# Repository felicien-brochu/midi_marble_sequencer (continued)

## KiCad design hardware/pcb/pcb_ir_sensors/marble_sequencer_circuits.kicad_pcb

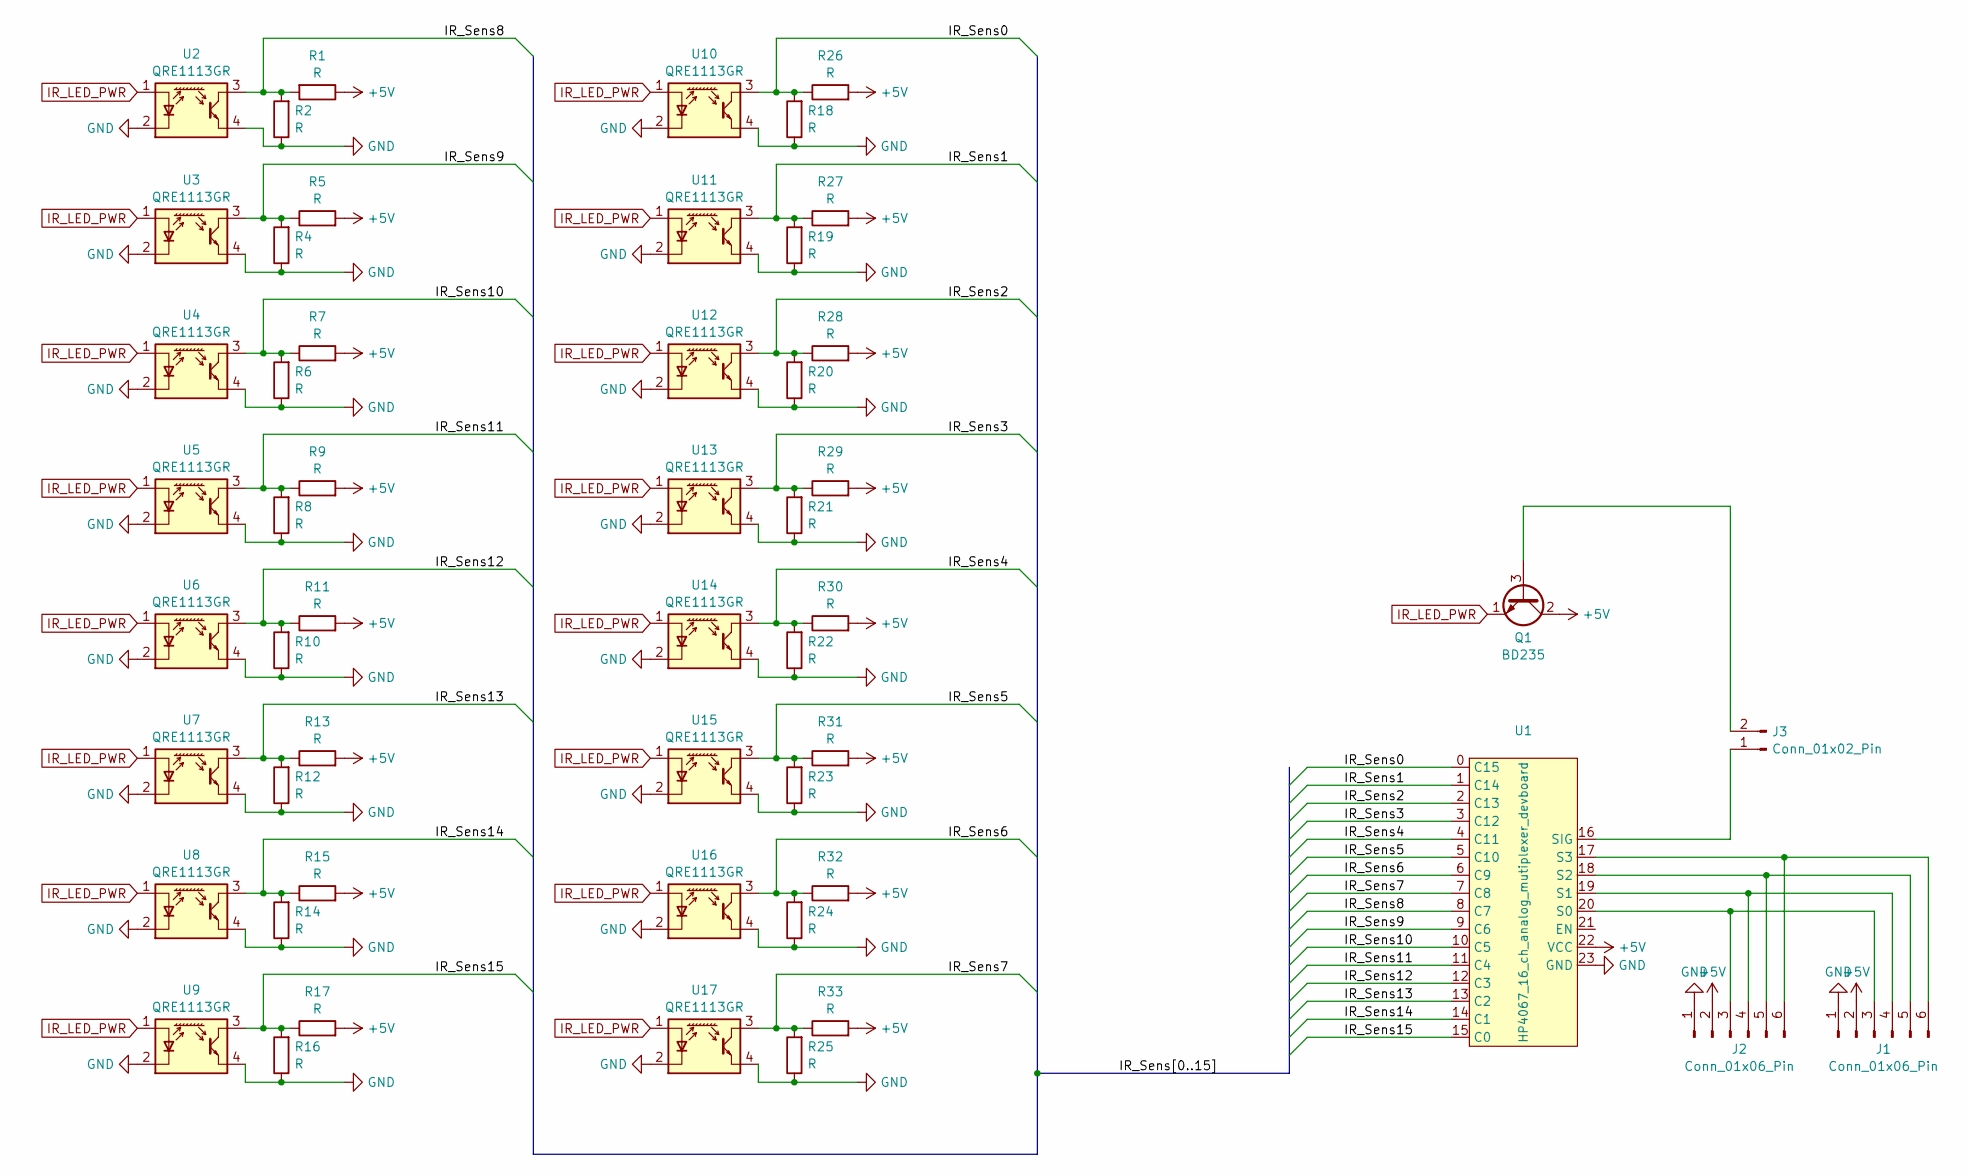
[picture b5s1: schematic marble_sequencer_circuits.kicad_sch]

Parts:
J1, J2: Conn_01x06_Pin; PinHeader_1x06_P2.54mm_Vertical
J3: Conn_01x02_Pin; PinHeader_1x02_P2.54mm_Vertical
Q1: BD235; TO-126-3_Vertical
R1, R2, R4, R5, R6, R7, R8, R9, R10, R11, R12, R13, R14, R15, R16, R17, R18, R19, R20, R21, R22, R23, R24, R25, R26, R27, R28, R29, R30, R31, R32, R33: R; R_Axial_DIN0207_L6.3mm_D2.5mm_P10.16mm_Horizontal_BIG_PADS
U1: HP4067_16_ch_analog_mutiplexer_devboard
U2, U3, U4, U5, U6, U7, U8, U9, U10, U11, U12, U13, U14, U15, U16, U17: QRE1113GR

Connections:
+5V: J1.2, J2.2, Q1.2 (C), R1.1, R5.2, R7.2, R9.2, R11.2, R13.2, R15.2, R17.2, R26.2, R27.2, R28.2, R29.2, R30.2, R31.2, R32.2, R33.2, U1.22 (VCC)
/IR_Sens0: R18.2, R26.1, U1.0 (C15), U10.3
/IR_Sens1: R19.2, R27.1, U1.1 (C14), U11.3
/IR_Sens2: R20.2, R28.1, U1.2 (C13), U12.3
/IR_Sens3: R21.2, R29.1, U1.3 (C12), U13.3
/IR_Sens4: R22.2, R30.1, U1.4 (C11), U14.3
/IR_Sens5: R23.2, R31.1, U1.5 (C10), U15.3
/IR_Sens6: R24.2, R32.1, U1.6 (C9), U16.3
/IR_Sens7: R25.2, R33.1, U1.7 (C8), U17.3
/IR_Sens8: R1.2, R2.2, U1.8 (C7), U2.3
/IR_Sens9: R4.2, R5.1, U1.9 (C6), U3.3
/IR_Sens10: R6.2, R7.1, U1.10 (C5), U4.3
/IR_Sens11: R8.2, R9.1, U1.11 (C4), U5.3
/IR_Sens12: R10.2, R11.1, U1.12 (C3), U6.3
/IR_Sens13: R12.2, R13.1, U1.13 (C2), U7.3
/IR_Sens14: R14.2, R15.1, U1.14 (C1), U8.3
/IR_Sens15: R16.2, R17.1, U1.15 (C0), U9.3
GND: J1.1, J2.1, R2.1, R4.1, R6.1, R8.1, R10.1, R12.1, R14.1, R16.1, R18.1, R19.1, R20.1, R21.1, R22.1, R23.1, R24.1, R25.1, U1.23 (GND), U2.2 (K), U2.4, U3.2 (K), U3.4, U4.2 (K), U4.4, U5.2 (K), U5.4, U6.2 (K), U6.4, U7.2 (K), U7.4, U8.2 (K), U8.4, U9.2 (K), U9.4, U10.2 (K), U10.4, U11.2 (K), U11.4, U12.2 (K), U12.4, U13.2 (K), U13.4, U14.2 (K), U14.4, U15.2 (K), U15.4, U16.2 (K), U16.4, U17.2 (K), U17.4
IR_LED_PWR: Q1.1 (E), U2.1 (A), U3.1 (A), U4.1 (A), U5.1 (A), U6.1 (A), U7.1 (A), U8.1 (A), U9.1 (A), U10.1 (A), U11.1 (A), U12.1 (A), U13.1 (A), U14.1 (A), U15.1 (A), U16.1 (A), U17.1 (A)
unnamed: J1.3, J2.3, U1.20 (S0)
unnamed: J1.4, J2.4, U1.19 (S1)
unnamed: J1.5, J2.5, U1.18 (S2)
unnamed: J1.6, J2.6, U1.17 (S3)
unnamed: J3.1, U1.16 (SIG)
unnamed: J3.2, Q1.3 (B)

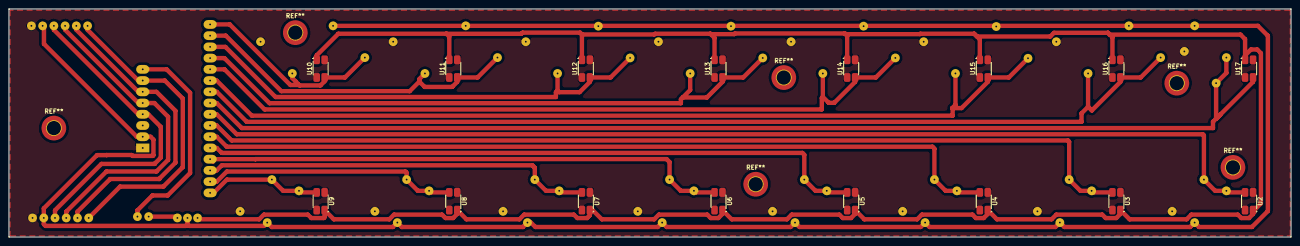
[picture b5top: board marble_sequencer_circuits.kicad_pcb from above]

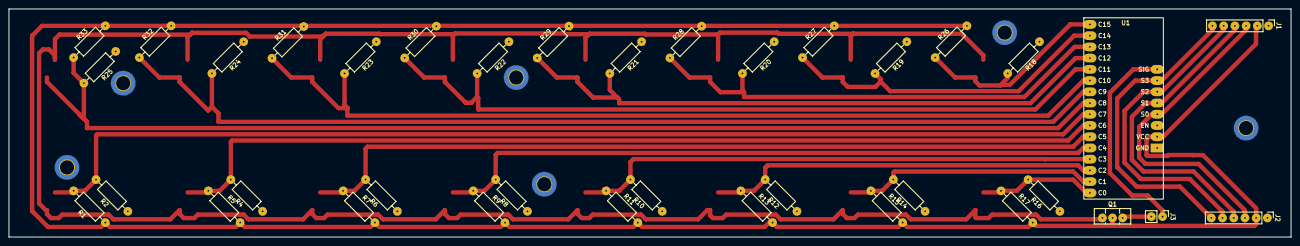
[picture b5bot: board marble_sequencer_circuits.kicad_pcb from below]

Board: 2 copper layers, 290.0 x 51.6 mm, 53 parts (37 on the bottom side), 25 nets.

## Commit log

2025-04-23 Hardware.
2025-04-23 Base code for main esp32. LED Snake example running.
2025-04-25 Base code for multiple IR Sensor boards + code to print first sensor of each board to calibrate LEDs power for each board using the potentiometers.
2025-07-22 Calibration and base midi controller code.
2025-07-22 Create midi_marble_sequencer_controls_tracks esp-idf project and extract common code in common_src folder.
2025-07-23 Classes for each physical actuator managed by main controls board.
2025-07-26 i2c communication between main and controls_main.
2025-07-28 BPM Timer and SequencerPage notions.
2025-07-29 Measure states updated. SKIP state works. LED Snake don't use blink scheme anymore.
2025-07-29 Make i2c communication more reliable.
2025-07-29 LOCK measure state works.
2025-07-30 Calibration change threshold computation.
2025-07-30 New MIDI mapping.
2025-07-30 New calibration data.
2025-07-31 Add CRC check for i2c transactions.
2025-07-31 Tracks mute buttons work.
2025-10-17 Clean PCB repo.
2025-10-17 First version using GPTimer.
2025-10-17 Upgrade esp_tinyusb and use esp-idf v5.5.1.
2025-10-17 Clean software directory. Delete old code.
2025-11-05 First correct communication between main and controls_main. ESP-IDF i2c slave driver is garbage: had to use arduinoesp32 framework instead.
2025-11-05 i2c communication between esp32 boards working.
2025-11-06 BPM displayed on play/pause LED.
2025-11-10 Calibration procedure with LED display. Calibration data saved and retreived from Non Volatile Storage (NVS).
2025-11-11 Statistics for sensor distribution.
2025-11-13 Current page LED blink. Start of page handling.
2025-11-14 Restart blink clock when changing blinking led.
2025-11-14 Blink current playing page even when it is programmed to stop playing afterwards.
2025-11-17 Live midi mapping.
2025-12-19 Flight case blueprint.
2025-12-19 Default Midi mapping.
2025-12-19 Midi mapping plugin made with JUCE.
2025-12-20 Calibration guide.
2025-12-20 Layout change for MidiMapperPlugin.
2026-01-06 Generate Readmes.
2026-01-06 Pages complete with soft lock on change.
2026-01-06 Play edited page midi notes on channels 8 to 15 for virtual playback on headphones.
2026-01-06 Edited page preview playback skips skippes measures.
2026-01-08 Edited page preview playback.
2026-01-08 Fix some bugs in Calibration and handle sensor boundaries saturation.
2026-01-09 New phase of calibration before sensor calibration: board calibration.
